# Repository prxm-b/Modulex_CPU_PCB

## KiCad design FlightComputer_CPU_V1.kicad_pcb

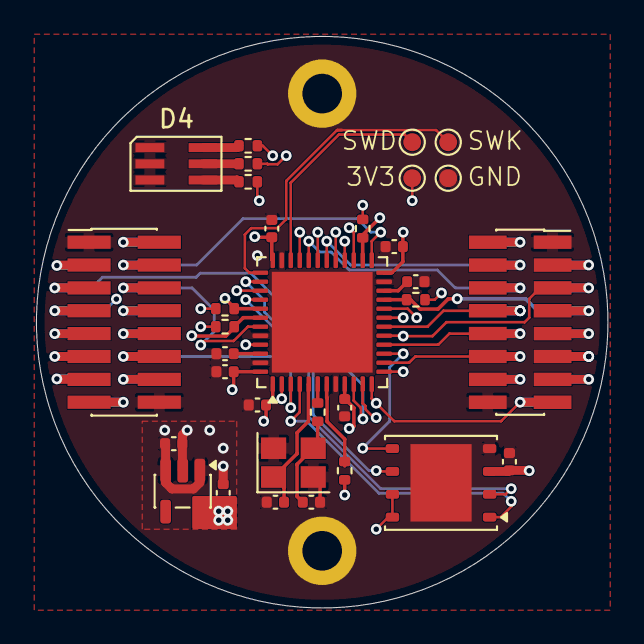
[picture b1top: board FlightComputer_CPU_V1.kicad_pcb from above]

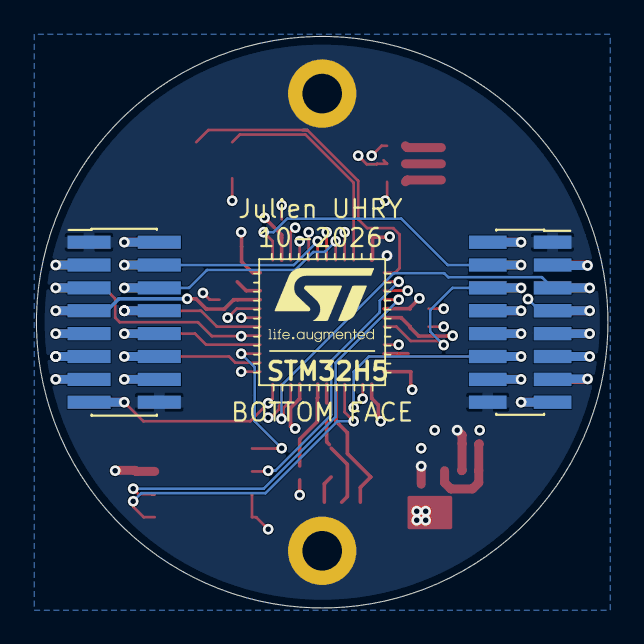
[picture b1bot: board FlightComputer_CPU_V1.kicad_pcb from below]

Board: 4 copper layers, 31.8 x 31.8 mm, 36 parts (2 on the bottom side), 44 nets.

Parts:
C10, C11, C12, C13, C14, C30: 100n; C_0402_1005Metric
C15, C16, C21: 2.2u; C_0402_1005Metric
C17, C18: 10p; C_0402_1005Metric
C20: 1u; C_0402_1005Metric
D4: LED_RGB; LED_Avago_PLCC6_3x2.8mm
H1, H2: MountingHole_Pad; MountingHole_2.2mm_M2_DIN965_Pad
J1: Female Back Left; PinSocket_2x08_P1.27mm_Vertical_SMD
J2: Male Back Right; PinHeader_2x08_P1.27mm_Vertical_SMD
J3: Male Front Left; PinHeader_2x08_P1.27mm_Vertical_SMD
J4: Female Front Right; PinSocket_2x08_P1.27mm_Vertical_SMD
R10: 100k; R_0402_1005Metric
R11, R12, R13, R14: 4.7k; R_0402_1005Metric
R15: 1.2k; R_0402_1005Metric
R40, R41, R42: 2.2k; R_0402_1005Metric
TP1, TP2, TP3, TP4: TestPoint; TestPoint_Pad_D1.0mm
U1: STM32H503CBUx; QFN-48-1EP_7x7mm_P0.5mm_EP5.6x5.6mm
U2: LD2981-3.3; SOT-23-5
U3: W25Q128JVP; WSON-8-1EP_6x5mm_P1.27mm_EP3.4x4.3mm
Y2: Crystal_GND24_Small; Crystal_SMD_Abracon_ABM8AIG-4Pin_3.2x2.5mm

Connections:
+3.3V: J1.2, J3.2
+3V3_CPU: C10.1, C11.1, C12.1, C13.1, C14.1, C21.1, C30.1, R10.2, R11.2, R12.1, R13.1, R14.1, TP3.1 (1_1), U1.1 (VBAT), U1.9 (VDDA), U1.24 (VDD), U1.36 (VDD), U1.48 (VDD), U2.5 (VOUT), U3.3 (~WP/IO_{2}), U3.7 (~HOLD/~RESET/IO_{3}), U3.8 (VCC)
+5V: C20.1, J1.3, J1.14, J2.3, J2.14, J3.3, J3.14, J4.3, J4.14, U2.1 (VIN), U2.3 (ON/~OFF)
/FDCAN1_RX: J1.4, J3.4, U1.25 (PB12)
/FDCAN1_TX: J1.6, J3.6, U1.43 (PB7)
/FLASH_CS: U1.4 (PC15), U3.1 (~CS)
/GPIO_1: J2.5, J4.5, U1.17 (PA7)
/GPIO_2: J1.12, J3.12, U1.3 (PC14)
/GPIO_3: J1.10, J3.10
/I2C1_SCL: J2.11, J4.11, R12.2, U1.42 (PB6)
/I2C1_SDA: J2.13, J4.13, R11.1, U1.41 (PB5)
/I2C2_SCL: J2.7, J4.7, R13.2, U1.21 (PB10)
/I2C2_SDA: J2.9, J4.9, R14.2, U1.26 (PB13)
/IRQ_1: J1.5, J3.5, U1.10 (PA0)
/IRQ_2: J1.7, J3.7, U1.19 (PB1)
/LEDB: R42.1, U1.45 (PB8)
/LEDG: R40.1, U1.39 (PB3(JTDO)
/LEDR: R41.1, U1.2 (PC13)
/NRST: R10.1, U1.7 (NRST)
/RCC_OSC_IN: C18.1, U1.5 (PH0), Y2.1
/RCC_OSC_OUT: R15.2, U1.6 (PH1)
/Reserved1: J1.15, J3.15
/Reserved2: J1.13, J3.13
/Reserved3: J1.11, J3.11
/SPI1_MISO: J2.10, J4.10, U1.16 (PA6)
/SPI1_MOSI: J2.12, J4.12, U1.14 (PA4)
/SPI1_SCK: J2.15, J4.15, U1.12 (PA2)
/SPI3_MISO: U1.40 (PB4(NJTRST)), U3.2 (DO/IO_{1})
/SPI3_MOSI: U1.15 (PA5), U3.5 (DI/IO_{0})
/SPI3_SCK: U1.38 (PA15(JTDI)), U3.6 (CLK)
/SWDCLK: TP2.1 (1_1), U1.37 (PA14(JTCK)
/SWDIO: TP1.1 (1_1), U1.34 (PA13(JTMS)
/USART1_RX: J2.2, J4.2, U1.11 (PA1)
/USART1_TX: J2.4, J4.4, U1.30 (PA9)
/USART2_RX: J2.6, J4.6, U1.32 (PA11)
/USART2_TX: J2.8, J4.8, U1.18 (PB0)
GND: C10.2, C11.2, C12.2, C13.2, C14.2, C15.1, C16.1, C17.2, C18.2, C20.2, C21.2, C30.2, D4.1 (RK), D4.2 (GK), D4.3 (BK), H1.1 (1_1), H2.1 (1_1), J1.1, J1.16, J2.1, J2.16, J3.1, J3.16, J4.1, J4.16, TP4.1 (1_1), U1.8 (VSSA), U1.23 (VSS), U1.35 (VSS), U1.44 (BOOT0), U1.47 (VSS), U1.49 (VSS), U2.2 (GND), U3.4 (GND), U3.9 (EP), Y2.2 (G), Y2.4 (G)
unnamed: C15.2, U1.46 (VCAP)
unnamed: C16.2, U1.22 (VCAP)
unnamed: C17.1, R15.1, Y2.3
unnamed: D4.4 (BA), R40.2
unnamed: D4.5 (GA), R41.2
unnamed: D4.6 (RA), R42.2
VBat: J1.8, J1.9, J3.8, J3.9
